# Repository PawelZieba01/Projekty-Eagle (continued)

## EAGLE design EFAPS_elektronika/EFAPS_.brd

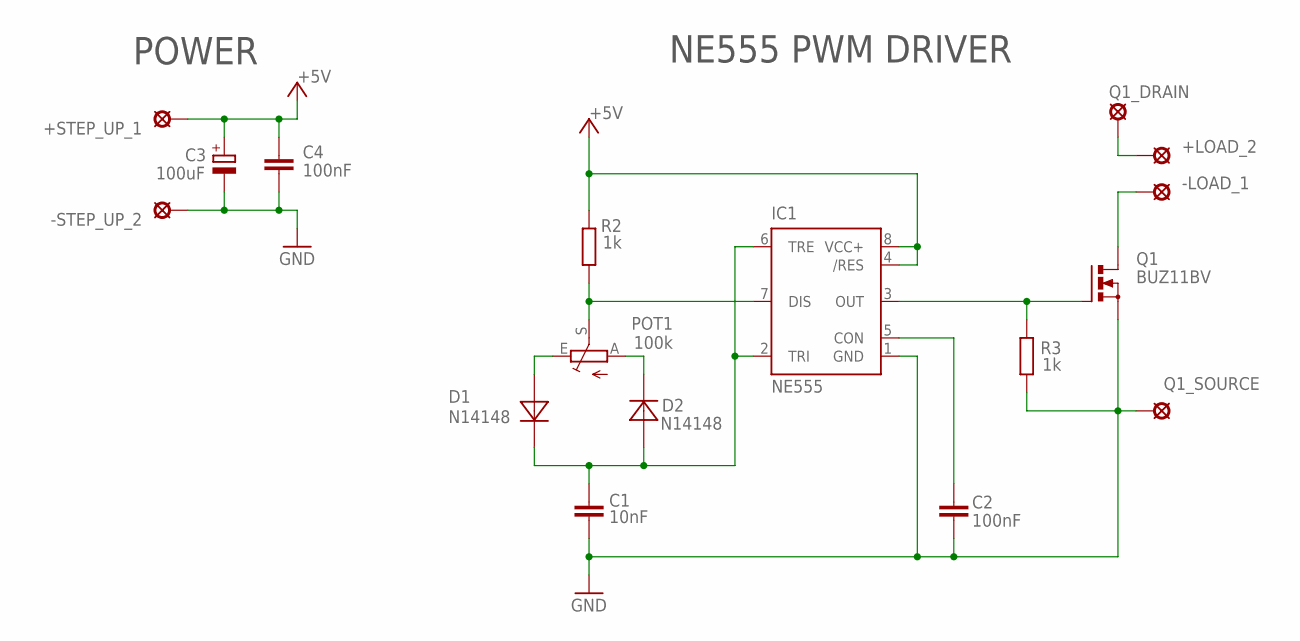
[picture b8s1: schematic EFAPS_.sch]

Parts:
+LOAD_2: SE14
+STEP_UP_1: SE14
-LOAD_1: SE14
-STEP_UP_2: SE14
C1: 10nF; C50-45-75
C2, C4: 100nF; C50-45-75
C3: 100uF; C5-8,5
D1, D2: N14148; DO35-7
IC1: NE555; DIL-08
POT1: 100k; CA6V
Q1: BUZ11BV; TO220BV
Q1_DRAIN, Q1_SOURCE: SE14
R2, R3: 1k; 204/7

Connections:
+5V: +STEP_UP_1.MP, C3.+, C4.P$1 (1), IC1.4 (/RES), IC1.8 (VCC+), R2.P$2 (2)
GND: -STEP_UP_2.MP, C1.P$2 (2), C2.P$2 (2), C3.-, C4.P$2 (2), IC1.1 (GND), Q1.S, Q1_SOURCE.MP, R3.P$1 (1)
unnamed: D1.+, POT1.E
unnamed: D2.-, POT1.A
unnamed: IC1.7 (DIS), POT1.S, R2.P$1 (1)
unnamed: IC1.3 (OUT), Q1.G, R3.P$2 (2)
unnamed: -LOAD_1.MP, Q1.D
unnamed: C1.P$1 (1), D1.-, D2.+, IC1.2 (TRI), IC1.6 (TRE)
unnamed: C2.P$1 (1), IC1.5 (CON)
unnamed: +LOAD_2.MP, Q1_DRAIN.MP

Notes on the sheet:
NE555 PWM DRIVER
POWER

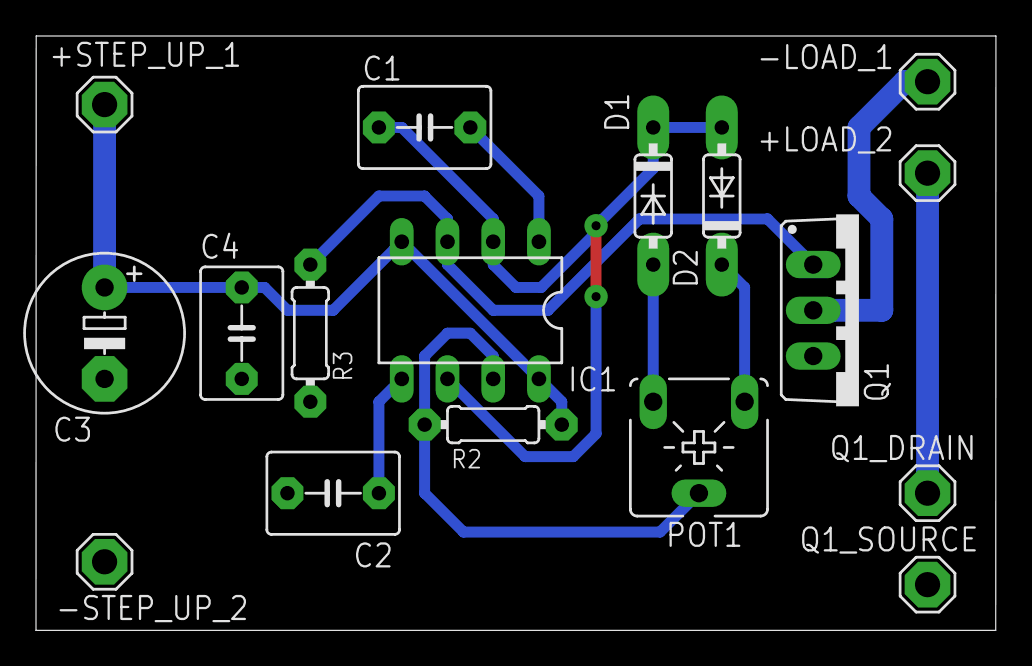
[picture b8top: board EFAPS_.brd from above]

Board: 2 copper layers, 53.3 x 33.0 mm, 17 parts (0 on the bottom side), 10 nets.
